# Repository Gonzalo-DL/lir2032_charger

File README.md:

# lir2032_charger
Cargador de baterias LIR2032 de Li-ion con buck 3.3v y bms.

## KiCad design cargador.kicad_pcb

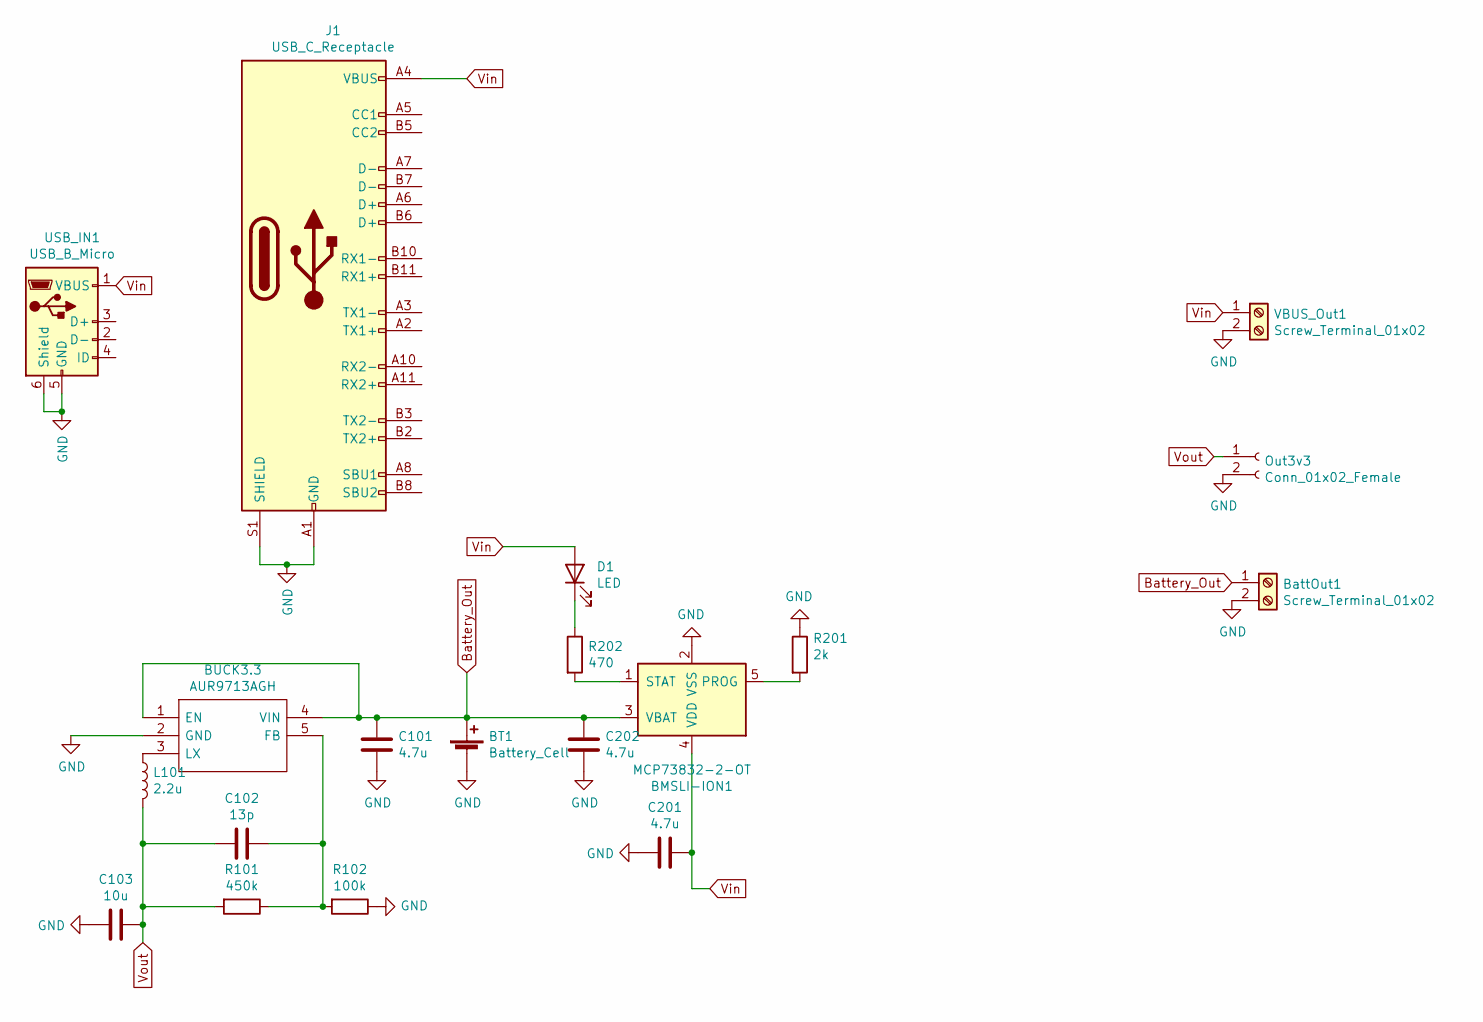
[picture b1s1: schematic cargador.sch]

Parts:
BMSLI-ION1: MCP73832-2-OT; SOT-23-5
BT1: Battery_Cell; BatteryHolder_Keystone_1058_1x2032
BUCK3.3: AUR9713AGH; SOT95P280X100-5N; Manufacturer_Part_Number AUR9713AGH; Mouser Part Number 621-AUR9713AGH
BattOut1: Screw_Terminal_01x02; TerminalBlock_bornier-2_P5.08mm
C101, C201, C202: 4.7u; C_0603_1608Metric
C102: 13p; C_0603_1608Metric
C103: 10u; C_0603_1608Metric
D1: LED; LED_0603_1608Metric
J1: USB_C_Receptacle; USB_C_Receptacle_Amphenol_12401610E4-2A
L101: 2.2u; L_0603_1608Metric
Out3v3: Conn_01x02_Female; PinHeader_1x02_P2.54mm_Vertical
R101: 450k; R_0603_1608Metric
R102: 100k; R_0603_1608Metric
R201: 2k; R_0603_1608Metric
R202: 470; R_0603_1608Metric
USB_IN1: USB_B_Micro; USB_Micro-B_GCT_USB3076-30-A
VBUS_Out1: Screw_Terminal_01x02; TerminalBlock_bornier-2_P5.08mm

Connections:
Battery_Out: BMSLI-ION1.3 (VBAT), BT1.1 (+), BUCK3.3.1 (EN), BUCK3.3.4 (VIN), BattOut1.1, C101.2, C202.1; also elsewhere on the board
GND: BMSLI-ION1.2 (VSS), BT1.2 (-), BUCK3.3.2 (GND), BattOut1.2, C101.1, C103.2, C201.1, C202.2, J1.A1 (GND), J1.A12 (GND), J1.B1 (GND), J1.B12 (GND), J1.S1 (SHIELD), Out3v3.2, R102.1, R201.1, USB_IN1.5 (GND), USB_IN1.6 (Shield), VBUS_Out1.2; also elsewhere on the board
unnamed: BMSLI-ION1.1 (STAT), R202.2
unnamed: BMSLI-ION1.5 (PROG), R201.2
unnamed: BUCK3.3.3 (LX), L101.1
unnamed: BUCK3.3.5 (FB), C102.1, R101.1, R102.2
unnamed: D1.1 (K), R202.1
Vin: BMSLI-ION1.4 (VDD), C201.2, D1.2 (A), J1.A4 (VBUS), J1.A9 (VBUS), J1.B4 (VBUS), J1.B9 (VBUS), USB_IN1.1 (VBUS), VBUS_Out1.1
Vout: C102.2, C103.1, L101.2, Out3v3.1, R101.2

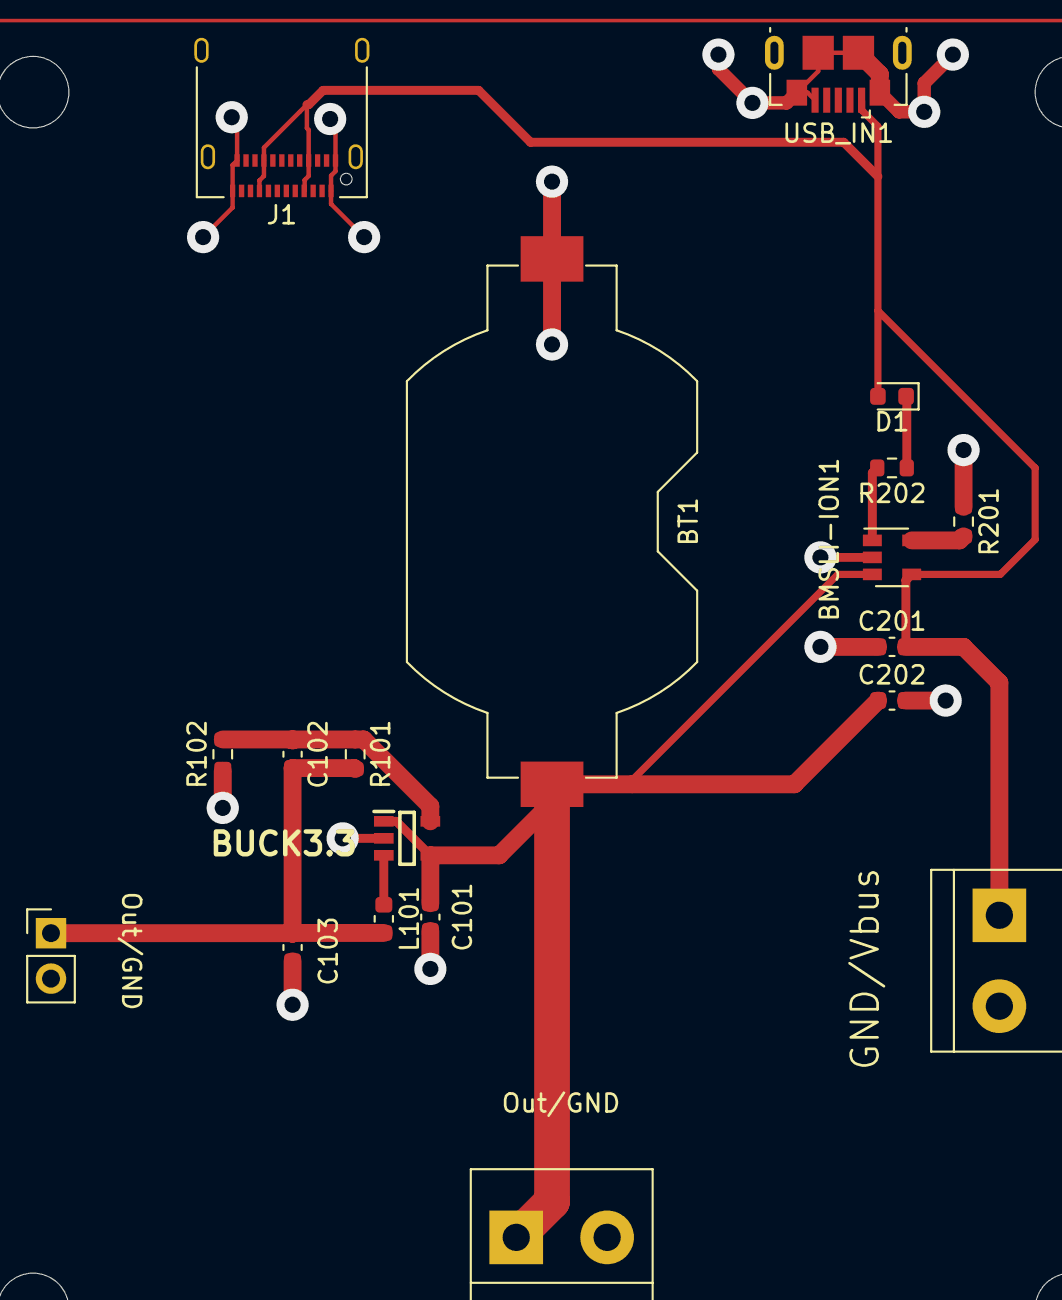
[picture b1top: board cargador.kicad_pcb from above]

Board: 2 copper layers, 20 parts (0 on the bottom side), 9 nets.

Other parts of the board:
 : MountingHole_4mm
BattOut: Screw_Terminal_01x02; TerminalBlock_bornier-2_P5.08mm

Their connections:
Battery_Out: BattOut.1; also elsewhere on the board
GND: BattOut.2; also elsewhere on the board
